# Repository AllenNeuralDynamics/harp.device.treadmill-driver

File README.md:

A Harp Device for controlling an instrumented variable-friction mouse treadmill

> [!NOTE]
> This repository contains design files for the electronics assembly. For the mechanical assembly, design files, and bill-of-materials, see the [OnShape project](https://cad.onshape.com/documents/579ff6de692121d8b6a45604/v/23e1e086e9eb645d096dac80/e/a0ad881c32324c0acf8e15df).

## Features
* linear (no switching!) current control of 12V magnetic brake, Placid Industries B5ZD, [datasheet](https://placidindustries.com/d/?h=a03be4b).
* reads measurements from an [RTS-10 torque transducer](https://www.transducertechniques.com/rts-torque-sensor.aspx#)
* wheatstone bridge input for torque transducer
* quadrature encoder input for position/speed measurements
* Harp-protocol compliant over full-speed USB
* accepts Harp time synchronization input.
* reverse-polarity protected power supply.

## Register Map
[List of Registers](./firmware/docs/register_map.csv)

## Credits
This board design was created in partnership with the team at [Second Order Effects](https://soeffects.com/).

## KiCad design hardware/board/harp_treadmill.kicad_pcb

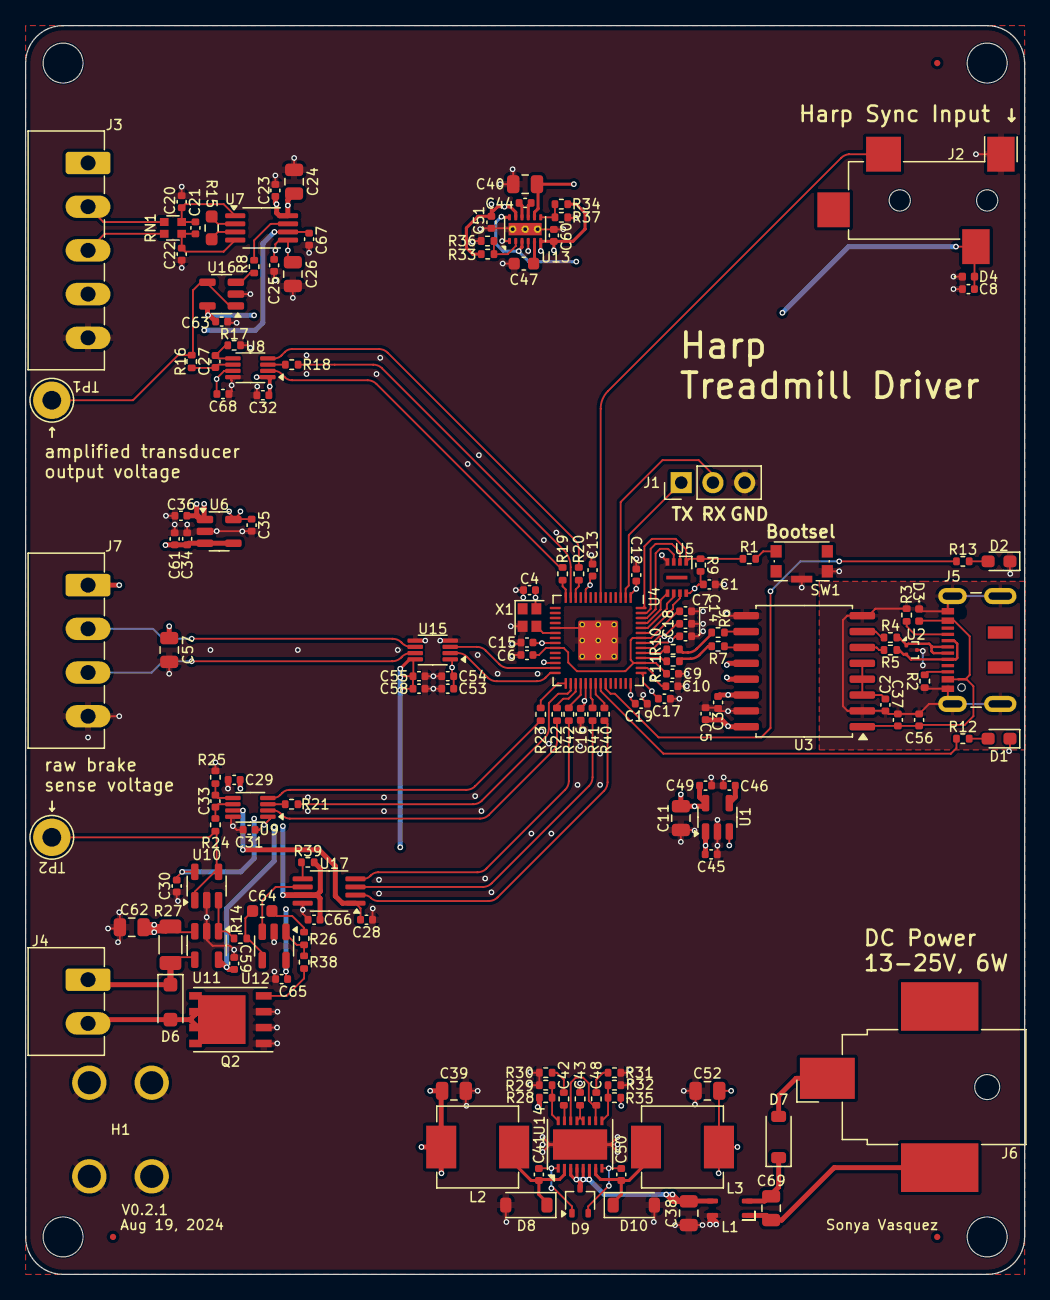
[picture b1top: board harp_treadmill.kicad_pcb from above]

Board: 4 copper layers, 80.0 x 100.0 mm, 157 parts (0 on the bottom side), 105 nets.

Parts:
C1, C2, C3, C5, C6, C7, C12, C13, C14, C15, C16, C17, C18, C19, C23, C25, C28, C29, C30, C31, C32, C34, C35, C36, C37, C41, C50, C53, C58, C59, C63, C65, C66, C67, C68: 100nF; C_0402_1005Metric
C4, C46: 10nF; C_0402_1005Metric
C8, C9, C10, C44, C45, C54, C55, C56, C61: 1uF; C_0402_1005Metric
C11, C24, C26, C38, C57, C62, C69: 10uF; C_0805_2012Metric
C20, C22: 100pF; C_0402_1005Metric
C21: 1000pF; C_0402_1005Metric
C27, C33: 300pF; C_0402_1005Metric
C39, C40, C52: 22uF; C_0805_2012Metric
C42, C48: 1.5nF; R_0402_1005Metric
C43: 4.7nF; R_0402_1005Metric
C47: 4.7uF; C_0603_1608Metric
C49, C51, C60: 2.2uF; C_0402_1005Metric
C64: 10nF; C_0603_1608Metric
D1, D2: LED; LED_0603_1608Metric_Pad1.05x0.95mm_HandSolder
D3, D4: D_TVS; D_0402_1005Metric
D6: 1N4007FL; D_SOD-123F
D7, D8, D10: D_Schottky; D_SOD-123
D9: BAT54AW; SOT-323_SC-70
FID1, FID2, FID3: Fiducial; Fiducial_0.5mm_Mask1mm
H1: MountingHole_Pad; Terminal_Keystone_779x_EdgeMount_Horizontal
J1: Conn_01x03_Male; PinHeader_1x03_P2.54mm_Vertical
J2: AudioJack3; Jack_3.5mm_CUI_SJ-3524-SMT_Horizontal
J3: Conn_01x05_Female; PhoenixContact_MC_1,5_5-G-3.5_1x05_P3.50mm_Horizontal
J4: Conn_01x02_Female; PhoenixContact_MC_1,5_2-G-3.5_1x02_P3.50mm_Horizontal
J5: USB_C_Receptacle_USB2.0; USB_C_Receptacle_JAE_DX07S016JA1R1500
J6: Barrel_Jack_Switch; BarrelJack_CUI_PJ-036AH-SMT_Horizontal
J7: Conn_01x04_Female; PhoenixContact_MC_1,5_4-G-3.5_1x04_P3.50mm_Horizontal
L1: L_Coupled_1423; L_CommonModeChoke_TDKCorporation_1210
L2, L3: 10uH; L_Vishay_IHLP-2525
Q2: Si7336ADP; PowerPAK_SO-8_Single
R1: 1K; R_0402_1005Metric
R2, R3, R26: 5K1; R_0402_1005Metric
R4, R5, R6, R7: 24; R_0402_1005Metric
R8, R9, R28, R30, R31, R35, R39: 10K; R_0402_1005Metric
R10, R11: 27; R_0402_1005Metric
R12, R13: 680; R_0402_1005Metric
R14: 7K5; R_0402_1005Metric
R15: 499; R_0603_1608Metric_Pad0.98x0.95mm_HandSolder
R16, R17, R24, R25: 100; R_0402_1005Metric
R18, R19, R20, R21, R22, R23, R40, R41, R42: 49.9; R_0402_1005Metric
R27: 0.08; R_1206_3216Metric
R29: 715; R_0402_1005Metric
R32: 1K82; R_0402_1005Metric
R33: 162K; R_0402_1005Metric
R34: 158K; R_0402_1005Metric
R36, R37: 51K; R_0402_1005Metric
R38: 10; R_0402_1005Metric
RN1: 20K; R_Array_Convex_2x0606
SW1: SW_Push_1P1T-SH_NO_Vertical_Wuerth_WS-TASV
TP1, TP2: TestPoint; TestPoint_THTPad_D3.0mm_Drill1.5mm
U1: LP2985-3.3; SOT-23-5
U2: TPD2EUSB30; Texas_DRT-3
U3: ADUM4160; SOIC-16W_7.5x10.3mm_P1.27mm
U4: RP2040; RP2040-QFN-56
U5: W25Q16JVUXIQ; Winbond-8USON-2x3mm
U6: REF2033; SOT-23-5
U7: AD8226; MSOP-8_3x3mm_P0.65mm
U8, U9: ADS7049; VSSOP-8_2.3x2mm_P0.5mm
U10, U12, U16: AD8615; TSOT-23-5
U11: INA180A4; SOT-23-5
U13: LM27762; WSON-12-1EP_3x2mm_P0.5mm_EP1x2.65_ThermalVias
U14: LT3506; DFN-16-1EP_4x5mm_P0.5mm_EP2.44x4.34mm
U15: 74LVCH2T45DC; VSSOP-8_2.3x2mm_P0.5mm
U17: LTC2641; MSOP-8_3x3mm_P0.65mm
X1: ECS-TXO-2016; Crystal_SMD_2016-4Pin_2.0x1.6mm

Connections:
5V2: C34.2, C40.1, C45.1, C52.1, C55.1, C57.1, C58.2, C61.1, C65.2, J7.1, L3.2, R35.1, U1.1 (VIN), U1.3 (ON/~OFF), U6.3 (EN), U6.4 (VIN), U12.5 (V+), U13.3 (VIN), U13.8 (EN-), U13.12 (EN+), U15.8 (VCCB)
+1V1: C6.2, C7.2, C9.1, U4.23 (DVDD), U4.45 (VREG_VOUT), U4.50 (DVDD)
+3V3: C1.2, C3.2, C4.2, C5.2, C8.1, C10.1, C11.1, C12.2, C13.2, C14.2, C15.2, C16.2, C17.2, C18.2, C19.2, C30.2, C31.2, C32.2, C49.2, C53.2, C54.1, C59.2, C63.2, C66.2, D4.2 (A2), J2.R, R9.2, R39.2, U1.5 (VOUT), U3.12 (PIN), U3.13 (SPD), U3.14 (VDD2), U3.16 (VBUS2), U4.1 (IOVDD), U4.10 (IOVDD), U4.22 (IOVDD), U4.26 (RUN), U4.33 (IOVDD), U4.42 (IOVDD), U4.43 (ADC_AVDD), U4.44 (VREG_IN), U4.48 (USB_VDD), U4.49 (IOVDD), U5.8 (VCC), U8.1 (DVDD), U9.1 (DVDD), U10.5 (V+), U11.5 (V+), U15.1 (VCCA), U16.5 (V+), U17.7 (VDD), X1.4 (VDD)
+5V: C23.2, C24.1, C51.2, J3.1, R33.1, U7.8 (V+), U13.11 (OUT+)
+12V: C39.1, C62.1, L2.1, R27.1, R28.2, U11.3 (+)
-5V: C25.2, C26.2, C60.2, J3.4, R34.1, U7.5 (V-), U13.6 (OUT-)
/Encoder/ENC_A: U4.27 (GPIO16), U15.3 (2A)
/Encoder/ENC_B: U4.28 (GPIO17), U15.2 (1A)
/Harp Core RP2040 + Isolated USB/D+: J5.A6 (D+), J5.B6 (D+), R4.1, U2.1 (D+)
/Harp Core RP2040 + Isolated USB/D-: J5.A7 (D-), J5.B7 (D-), R5.1, U2.2 (D-)
/Harp Core RP2040 + Isolated USB/DD+: R6.2, R10.2
/Harp Core RP2040 + Isolated USB/DD-: R7.2, R11.2
/Harp Core RP2040 + Isolated USB/HARP_CLK_SYNC: J2.T, U4.7 (GPIO5)
/Harp Core RP2040 + Isolated USB/PIO_ADC0_CS: R23.2, U4.29 (GPIO18)
/Harp Core RP2040 + Isolated USB/PIO_ADC0_POCI: R21.2, U4.30 (GPIO19)
/Harp Core RP2040 + Isolated USB/PIO_ADC0_SCK: R22.2, U4.31 (GPIO20)
/Harp Core RP2040 + Isolated USB/PIO_ADC1_CS: R20.2, U4.12 (GPIO9)
/Harp Core RP2040 + Isolated USB/PIO_ADC1_POCI: R18.2, U4.13 (GPIO10)
/Harp Core RP2040 + Isolated USB/PIO_ADC1_SCK: R19.2, U4.14 (GPIO11)
/Harp Core RP2040 + Isolated USB/PIO_DAC_CS: R40.2, U4.35 (GPIO23)
/Harp Core RP2040 + Isolated USB/PIO_DAC_PICO: R42.2, U4.32 (GPIO21)
/Harp Core RP2040 + Isolated USB/PIO_DAC_SCK: R41.2, U4.34 (GPIO22)
/Harp Core RP2040 + Isolated USB/QSPI_CLK: U4.52 (QSPI_SCLK), U5.6 (CLK)
/Harp Core RP2040 + Isolated USB/QSPI_CS: R1.2, R9.1, U4.56 (QSPI_SS), U5.1 (~CS)
/Harp Core RP2040 + Isolated USB/QSPI_D0: U4.53 (QSPI_SD0), U5.5 (DI(IO0))
/Harp Core RP2040 + Isolated USB/QSPI_D1: U4.55 (QSPI_SD1), U5.2 (DO(IO1))
/Harp Core RP2040 + Isolated USB/QSPI_D2: U4.54 (QSPI_SD2), U5.3 (IO2)
/Harp Core RP2040 + Isolated USB/QSPI_D3: U4.51 (QSPI_SD3), U5.7 (IO3)
/Harp Core RP2040 + Isolated USB/UART0_RXD: J1.2, U4.3 (GPIO1)
/Harp Core RP2040 + Isolated USB/UART0_TXD: J1.1, U4.2 (GPIO0)
/Harp Core RP2040 + Isolated USB/USB_Boot: R1.1, SW1.2
/Harp Core RP2040 + Isolated USB/VDD1: C2.2, U3.3 (VDD1), U3.4 (PDEN), U3.5 (SPU)
GND: C1.1, C3.1, C4.1, C5.1, C6.1, C7.1, C8.2, C9.2, C10.2, C11.2, C12.1, C13.1, C14.1, C15.1, C16.1, C17.1, C18.1, C19.1, C20.1, C22.2, C23.1, C24.2, C25.1, C26.1, C28.1, C29.1, C30.1, C31.1, C32.1, C34.1, C35.1, C36.1, C38.2, C39.2, C40.2, C43.1, C45.2, C46.2, C47.2, C49.1, C51.1, C52.2, C53.1, C54.2, C55.2, C57.2, C58.1, C59.1, C60.1, C61.2, C62.2, C63.1, C65.1, C66.1, C67.1, C68.1, D1.1 (K), D2.1 (K), D4.1 (A1), D8.2 (A), D10.2 (A), H1.1, J1.3, J2.S, J3.5, J7.4, L1.4, Q2.1 (S), Q2.2 (S), Q2.3 (S), R17.1, R25.1, R29.2, R30.1, R31.1, R32.1, R36.2, R37.2, SW1.4, SW1.SH, U1.2 (GND), U3.9 (GND2), U3.15 (GND2), U4.19 (TESTEN), U4.57 (GND), U5.4 (GND), U6.2 (GND), U8.8 (GND), U9.8 (GND), U10.2 (V-), U11.2 (GND), U12.2 (V-), U13.1 (PGOOD), U13.4 (GND), U13.13 (PAD), U14.17 (GND), U15.4 (GND), U15.5 (DIR), U16.2 (V-), U17.8 (GND), X1.2 (GND)
GND1: C2.1, C37.1, C56.2, D3.1 (A1), J5.A1 (GND), J5.A12 (GND), J5.B1 (GND), J5.B12 (GND), J5.S1 (SHIELD), R2.2, R3.2, U2.3 (GND), U3.2 (GND1), U3.8 (GND1)
GND2: C69.2, J6.2, L1.1
unnamed: C42.1, R30.2
unnamed: C48.2, R31.2
unnamed: C64.2, R26.1
unnamed: D1.2 (A), R12.2
unnamed: D2.2 (A), R13.2
unnamed: D6.2 (A), J4.2, Q2.5 (D)
unnamed: D6.1 (K), J4.1, R27.2, U11.4 (-)
unnamed: C69.1, D7.1 (K), L1.2
unnamed: C41.1, D8.1 (K), L2.2, U14.2 (SW1)
unnamed: C50.1, D10.1 (K), L3.1, U14.7 (SW2)
unnamed: J3.2, RN1.1 (R1.1)
unnamed: J3.3, RN1.2 (R2.1)
unnamed: J5.A5 (CC1), R2.1
unnamed: J5.B5 (CC2), R3.1
unnamed: J7.2, U15.6 (2B)
unnamed: J7.3, U15.7 (1B)
unnamed: Q2.4 (G), R38.2
unnamed: R15.1, U7.2 (RG)
unnamed: R15.2, U7.3 (RG)
unnamed: R26.2, R38.1, U12.1
unnamed: C20.2, C21.1, RN1.4 (R1.2), U7.1 (IN-)
unnamed: C21.2, C22.1, RN1.3 (R2.2), U7.4 (IN+)
unnamed: C46.1, U1.4 (BP)
unnamed: R6.1, U3.10 (DD+)
unnamed: R7.1, U3.11 (DD-)
unnamed: R4.2, U3.7 (UD+)
unnamed: R5.2, U3.6 (UD-)
unnamed: R12.1, U4.36 (GPIO24)
unnamed: R13.1, U4.37 (GPIO25)
unnamed: R11.1, U4.46 (USB_DM)
unnamed: R10.1, U4.47 (USB_DP)
unnamed: U4.20 (XIN), X1.3 (OUT)
unnamed: R8.2, U7.7 (VOUT)
unnamed: C27.2, R17.2, U8.5 (AINM)
unnamed: C27.1, R16.1, U8.6 (AINP)
unnamed: R19.1, U8.2 (SCLK)
unnamed: R18.1, U8.3 (SDO)
unnamed: R20.1, U8.4 (~CS)
unnamed: C33.2, R25.2, U9.5 (AINM)
unnamed: C33.1, R24.1, U9.6 (AINP)
unnamed: R22.1, U9.2 (SCLK)
unnamed: R21.1, U9.3 (SDO)
unnamed: R23.1, U9.4 (~CS)
unnamed: R14.1, U10.3 (+), U11.1
unnamed: R24.2, TP2.1, U10.1, U10.4 (-)
unnamed: U12.3 (+), U17.6 (VOUT)
unnamed: C64.1, R14.2, U12.4 (-)
unnamed: C44.1, U13.10 (C+)
unnamed: C44.2, U13.9 (C-)
unnamed: C47.1, U13.5 (CP)
unnamed: R33.2, R36.1, U13.2 (FB+)
unnamed: R34.2, R37.1, U13.7 (FB-)
unnamed: C41.2, D9.1, U14.1 (BOOST1)
unnamed: C50.2, D9.2, U14.8 (BOOST2)
unnamed: R28.1, R29.1, U14.16 (FB1)
unnamed: R32.2, R35.2, U14.9 (FB2)
unnamed: C48.1, U14.10 (VC2), U14.14 (PG1)
unnamed: C43.2, U14.12 (RUN/SS2), U14.13 (RUN/SS1)
unnamed: C42.2, U14.15 (VC1)
unnamed: R8.1, U16.3 (+)
unnamed: R16.2, TP1.1, U16.1, U16.4 (-)
unnamed: R42.1, U17.4 (DIN)
unnamed: R41.1, U17.3 (SCLK)
unnamed: R39.1, U17.5 (~CLR)
unnamed: R40.1, U17.2 (~CS)
VBUS: C37.2, C56.1, D3.2 (A2), J5.A4 (VBUS), J5.A9 (VBUS), J5.B4 (VBUS), J5.B9 (VBUS), U3.1 (VBUS1)
VIN1: C38.1, D9.3, L1.3, U14.3 (VIN1), U14.4 (VIN1), U14.5 (VIN2), U14.6 (VIN2)
VPP: D7.2 (A), J6.1
VREF_1V65: C36.2, C67.2, U6.1 (VBIAS), U7.6 (REF)
VREF_3V3: C28.2, C29.2, C35.2, C68.2, U6.5 (VREF), U8.7 (AVDD), U9.7 (AVDD), U17.1 (REF)

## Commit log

2023-04-10 add schematic draft
2023-04-11 update cmakelists to compile harp core
2023-04-14 draft torque load sensing in schematic
2023-04-15 adc reading works
2023-05-09 debug port works; draft current driver
2023-05-09 add preliminary register map.
2023-10-17 rename git submodule
2023-10-18 update board schematic
2023-10-19 update pcb
2023-10-20 update schematic
2023-10-26 update sch and pcb
2023-10-27 update schematic; continue pcb draft
2023-10-27 wrap up pcb draft
2023-10-27 update hw license
2023-10-27 add notes
2023-10-30 update schematic annotation
2023-11-09 draft layout with analog brake driver circuit
2023-11-14 draft v0.1 pcb
2023-12-06 draft firmware
2023-12-11 draft main.cpp
2023-12-14 draft of firmware works
2023-12-22 fix 12-bit adc bug
2023-12-22 remove embedded submodule
2023-12-22 add adc lib submodule and remove pico sdk submodule
2024-01-10 add cad v0.2.0 step model
2024-01-10 draft lid
2024-01-10 add lids
2024-01-10 update lids
2024-01-10 add lid dxfs
2024-01-12 add firmware license
2024-02-27 Add first draft of interface
2024-03-06 Update according to new specs
2024-03-06 Improve clarity
2024-03-06 Fix package metadata
2024-03-06 Regenerate interface
2024-03-08 update register draft
2024-03-08 add bulk sensor reading example
2024-03-08 adding untare capability
2024-03-08 add separate read-sensor example
2024-03-08 update tare register
2024-03-08 fix event register update bug
2024-03-08 Update schema
2024-03-08 Add register metadata
2024-03-08 update comment
2024-03-21 Standardize folder structure across allen devices
2024-06-14 add comment about race condition
2024-06-14 bugfix uart port
2024-07-18 Fix data format for DispatchRate register
2024-07-18 Bump package
2024-07-18 draft torque limiting
2024-07-18 update torque limiting logic
2024-07-18 prevent EVENT msg spam when torque limit triggered.
2024-07-24 append git has to executable name
2024-07-25 add filter to torque limit sensing; bugfix reg_count
2024-07-26 offset treadmill limits
2024-07-26 add pyharp examples
2024-07-29 migrate ltc264x lib to submodule
2024-08-13 add code comment
2024-08-13 draft brake calibration scripts
2024-08-20 draft brake calibration code
2024-08-20 update silkscreen size; add mating connector note
2024-08-20 update brake calibration script
2024-08-21 draft working calibration script
2024-08-21 Update device spec to latest firmware updates
2024-08-21 Remove string literals
2024-08-21 Regenerate interfaces
2024-08-21 Update package metadata with release
2024-08-21 add requirements.txt
2024-08-21 update calibration readme
2024-08-21 Clarify default behavior of EnableTorqueLimit register
2024-08-21 get writing settings working
2024-08-24 add calibration output-to-csv option
2024-08-26 update calibration script
2024-08-26 add slow sleep
2024-08-26 add duration calculation info msg
2024-08-27 add trim to enclosure
2024-09-24 draft curve fit
2024-09-25 update pcb and schematic
2024-09-25 update harp core and add hw/fw version to harp core
2024-09-26 add frontfacing images
2024-10-02 update for windows compatibility
2024-10-11 add rrio note about ad8226
2024-11-08 Update bonsai generators
2024-11-09 Fix schema source
2024-11-10 Favor harp-tech as source of device schema
2025-02-11 update harp core & bump version
2025-02-11 add description to usb-descriptors
2025-02-11 update version number
